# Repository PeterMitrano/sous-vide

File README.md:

# Sous-Vide

My first PCB design project.

### Final Results!

### Materials

see [sous-vide_bom.csv](./kicad_proj/sous-vide_bom_0.3.csv)

### Schematic

see [sous-vide.sch](./kicad_proj/sous-vide.sch)

### PCB

see [sous-vide.kicad_pcb](./kicad_proj/sous-vide.kicad_pcb)

Mains power is scary. I used this to calculate trace width/clearance: http://www.desmith.net/NMdS/Electronics/TraceWidth.html

### Revision Notes

 - Hole size of screw terminals are too small. Should be 1.8542mm
 - Screw terminals are a bad idea, use IEC connector
 - Higher power heater
 - Buzzer/Dinger!
 - One wire for thermistor/heater
 - Something to stir the water around
 - Label on V+ and V- on heater are backwards (J1)
 - Button footprint is wrong

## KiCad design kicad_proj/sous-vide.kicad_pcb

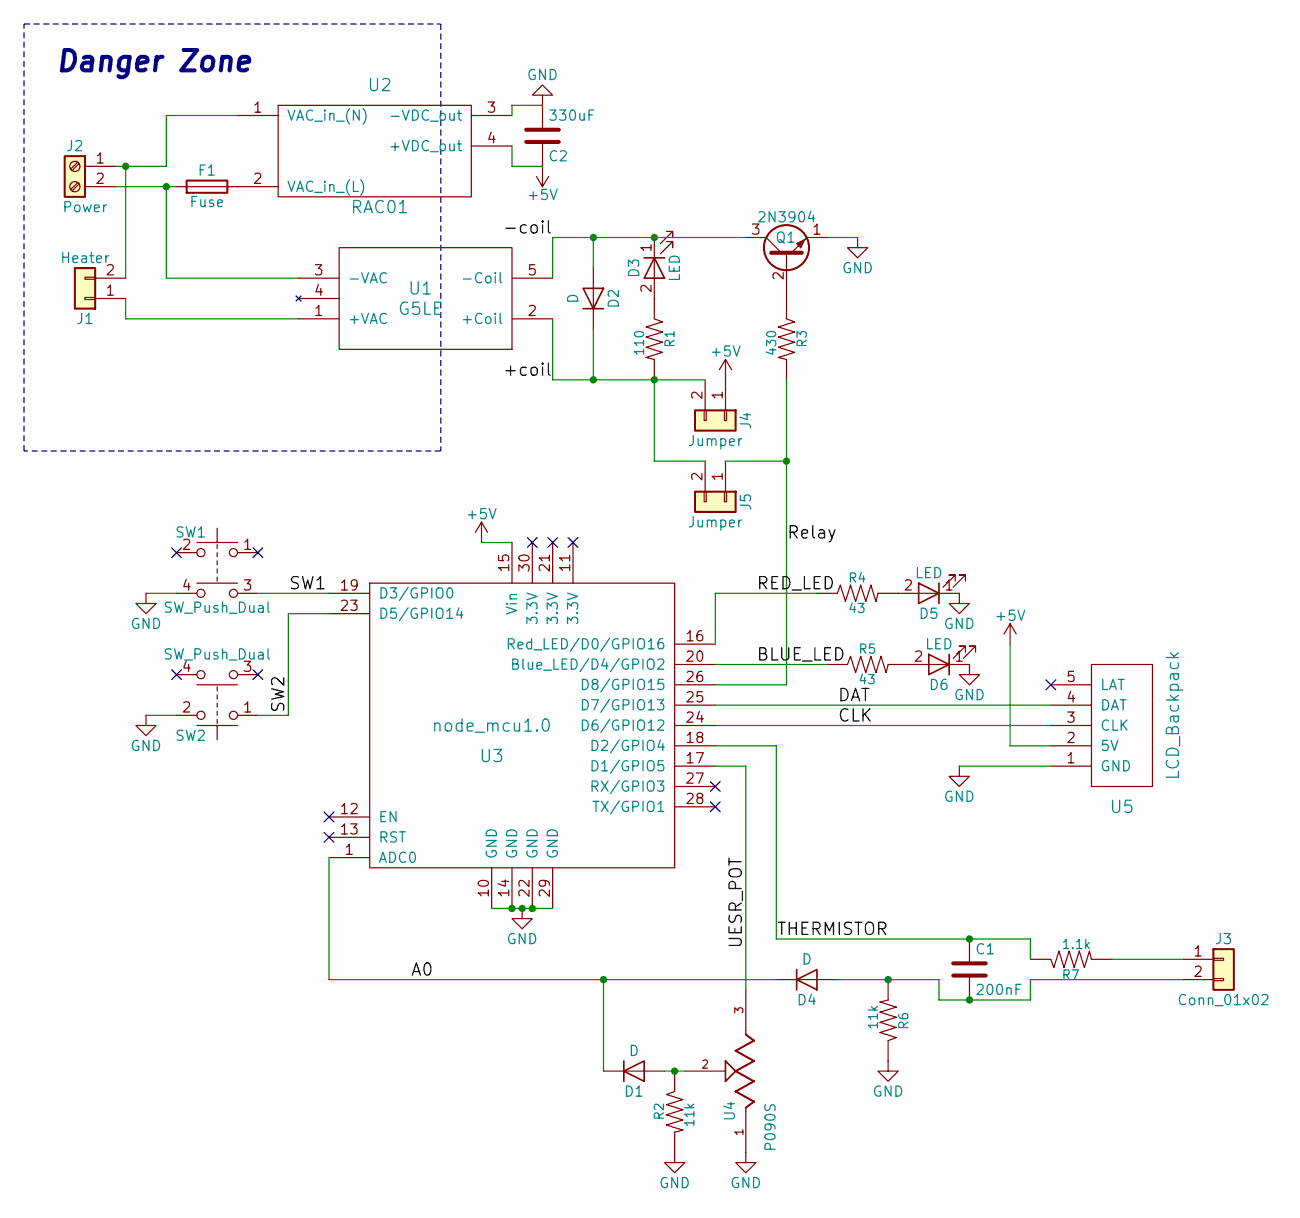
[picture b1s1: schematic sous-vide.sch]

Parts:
C1: 200nF; C_Disc_D4.3mm_W1.9mm_P5.00mm
C2: 330uF; CP_Radial_D8.0mm_P3.50mm
D1, D2, D4: D; D_DO-35_SOD27_P7.62mm_Horizontal; Part # 1N4148FS-ND
D3, D5, D6: LED; LED_D5.0mm; Part # 67-1105-ND
F1: Fuse; Fuse_Holder_65600001009
J1: Heater; NC6-P108-02
J2: Power; NC6-P108-02
J3: Conn_01x02; Pin_Header_Straight_1x02_Pitch2.54mm
J4, J5: Jumper; Pin_Header_Straight_1x02_Pitch2.54mm
Q1: 2N3904; TO-92_Molded_Narrow
R1: 110; R_Axial_DIN0207_L6.3mm_D2.5mm_P10.16mm_Horizontal
R2, R6: 11k; R_Axial_DIN0207_L6.3mm_D2.5mm_P10.16mm_Horizontal
R3: 430; R_Axial_DIN0207_L6.3mm_D2.5mm_P10.16mm_Horizontal
R4, R5: 43; R_Axial_DIN0207_L6.3mm_D2.5mm_P10.16mm_Horizontal
R7: 1.1k; R_Axial_DIN0207_L6.3mm_D2.5mm_P10.16mm_Horizontal
SW1, SW2: SW_Push_Dual; SW_TH_Tactile_Omron_B3F-10xx; Part # SW400-ND
U1: G5LE; Relay_SPDT_OMRON-G5LE-1
U2: RAC01; RAC01-05SC
U3: node_mcu1.0; NodeMCU_1_0
U4: P090S; P090S-THT_MNT
U5: LCD_Backpack; Pin_Header_Straight_1x05_Pitch2.54mm

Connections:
+5V: C2.1, J4.1, U2.4 (+VDC_out), U3.15 (Vin), U5.2 (5V)
/+coil: D2.1 (K), J4.2, J5.2, R1.2, U1.2 (+Coil)
/-coil: D2.2 (A), D3.1 (K), Q1.3 (C), U1.5 (-Coil)
/A0: D1.1 (K), D4.1 (K), U3.1 (ADC0)
/BLUE_LED: R5.1, U3.20 (Blue_LED/D4/GPIO2)
/CLK: U3.24 (D6/GPIO12), U5.3 (CLK)
/DAT: U3.25 (D7/GPIO13), U5.4 (DAT)
/RED_LED: R4.1, U3.16 (Red_LED/D0/GPIO16)
/Relay: J5.1, R3.2, U3.26 (D8/GPIO15)
/SW1: SW1.3, U3.19 (D3/GPIO0)
/SW2: SW2.1, U3.23 (D5/GPIO14)
/THERMISTOR: C1.1, R7.1, U3.18 (D2/GPIO4)
/UESR_POT: U3.17 (D1/GPIO5), U4.3 (CW)
GND: C2.2, D5.1 (K), D6.1 (K), Q1.1 (E), R2.2, R6.1, SW1.4, SW2.2, U2.3 (-VDC_out), U3.10 (GND), U3.14 (GND), U3.22 (GND), U3.29 (GND), U4.1 (CCW), U5.1 (GND)
unnamed: C1.2, D4.2 (A), J3.2, R6.2
unnamed: D1.2 (A), R2.1, U4.2 (S)
unnamed: D3.2 (A), R1.1
unnamed: D5.2 (A), R4.2
unnamed: D6.2 (A), R5.2
unnamed: F1.1, U2.2 (VAC_in_(L))
unnamed: F1.2, J2.2, U1.3 (-VAC)
unnamed: J1.1, U1.1 (+VAC)
unnamed: J1.2, J2.1, U2.1 (VAC_in_(N))
unnamed: J3.1, R7.2
unnamed: Q1.2 (B), R3.1

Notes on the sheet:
Danger Zone

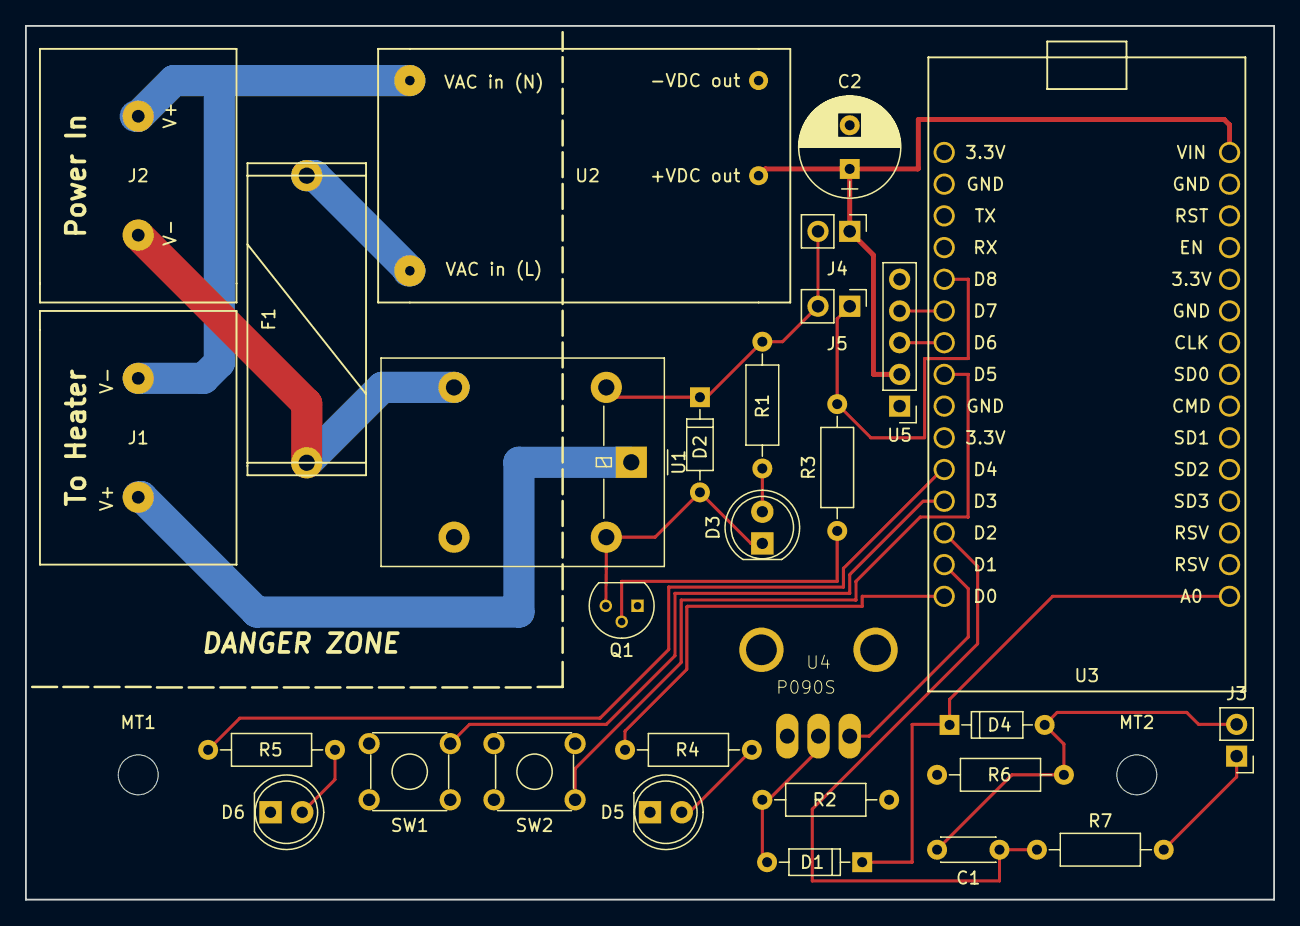
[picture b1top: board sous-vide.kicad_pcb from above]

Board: 2 copper layers, 100.0 x 70.0 mm, 31 parts (0 on the bottom side), 25 nets.

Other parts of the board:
MT1, MT2: MountingHole_3.2mm_M3

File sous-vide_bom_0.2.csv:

Component,Description,Part,References,Value,Footprint,Quantity Per PCB,Datasheet,Part #,Field8,Field4,Field7,Field6,Field5
1,Unpolarized capacitor,C,C1,C,C_Disc_D4.3mm_W1.9mm_P5.00mm,1,,,,,,,
2,Diode,D,D1 D2 D4,D,D_DO-35_SOD27_P7.62mm_Horizontal,3,https://www.fairchildsemi.com/datasheets/1N/1N914.pdf,1N4148FS-ND,,,,,
3,LED generic,LED,D3 D5 D6,LED,LED_D5.0mm,3,http://www.lumex.com/content/files/ProductAttachment/SSL-LX5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,67-1105-ND,,,,,
4,"Generic connector, single row, 01x02",Conn_01x02,J1,Conn_01x02,NC6-P108-02,1,,,,,,,
5,"Generic screw terminal, single row, 01x02",Screw_Terminal_01x02,J2,Conn_01x02,NC6-P108-02,1,,,,,,,
6,"Generic connector, single row, 01x02",Conn_01x02,J3,Conn_01x02,Pin_Header_Straight_1x02_Pitch2.54mm,1,,,,,,,
7,"40V Vce, 0.2A Ic, NPN, Small Signal Transistor, TO-92",2N3904,Q1,2N3904,TO-92_Molded_Narrow,1,https://www.fairchildsemi.com/datasheets/MM/MMBT3904.pdf,,,,,,
8,Generic Resistor Package,RESISTOR0402,R7,1.1k,R_Axial_DIN0207_L6.3mm_D2.5mm_P10.16mm_Horizontal,1,,,,,,,
9,Generic Resistor Package,RESISTOR0402,R1,110,R_Axial_DIN0207_L6.3mm_D2.5mm_P10.16mm_Horizontal,1,,,,,,,
10,Generic Resistor Package,RESISTOR0402,R2 R6,11k,R_Axial_DIN0207_L6.3mm_D2.5mm_P10.16mm_Horizontal,2,,,,,,,
11,Generic Resistor Package,RESISTOR0402,R4 R5,43,R_Axial_DIN0207_L6.3mm_D2.5mm_P10.16mm_Horizontal,2,,,,,,,
12,"Push button switch, generic, symbol, four pins",SW_Push_Dual,SW1 SW2,SW_Push_Dual,SW_TH_Tactile_Omron_B3F-10xx,2,http://omronfs.omron.com/en_US/ecb/products/pdf/en-b3f.pdf,SW400-ND,,,,,
13,,G5LE,U1,G5LE,Relay_SPDT_OMRON-G5LE-1,1,https://media.digikey.com/pdf/Data%20Sheets/Omron%20PDFs/G5L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,,,,,,
14,,LCD_Backpack,U5,LCD_Backpack,Pin_Header_Straight_1x05_Pitch2.54mm,1,,,,,,,
15,,P090S-04F20BR10K,U4,P090S,P090S-THT_MNT,1,P090S-04F20BR10K,,TT Electronics/BI,Good,None,0.40 USD,Res Conductive Plastic POT 10K Ohm 20% 0.03W 1(Elec)/1(Mech)Turn 6mm (11.4 X 12.65 X 23mm) Pin Bracket Mount/Through ...
16,,RAC01,U2,RAC01,RAC01-05SC,1,https://www.recom-power.com/pdf/Powerline-AC-DC/RAC01_02-SC.pdf,,,,,,
17,,node_mcu1.0,U3,node_mcu1.0,NodeMCU_1_0,1,,,,,,,





Component Groups:,17
Component Count:,24
Fitted Components:,24
Number of PCBs:,1
Total components:,24
Schematic Version:,0.2
Schematic Date:,2017-12-28
BoM Date:,Mon 01 Jan 2018 16:54:34 EST
Schematic Source:,/home/peter/Projects/sous-vide/sous-vide.sch
KiCad Version:,Eeschema 4.0.7-e2-6376~58~ubuntu16.04.1

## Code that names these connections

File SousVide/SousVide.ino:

#include <Wire.h>

const unsigned int RED_LED = D0;
const unsigned int BLUE_LED = D4;
const unsigned int SW1 = D3;
const unsigned int SW2 = D5;
const unsigned int RELAY = D8;
const unsigned int DAT = D7;
const unsigned int CLK = D6;
const unsigned int POT = D1;
const unsigned int THRM = D2;

unsigned long t = 0;
bool relay_state = false;

void setup() {
  pinMode(RED_LED, OUTPUT);
  pinMode(BLUE_LED, OUTPUT);
  pinMode(SW1, INPUT_PULLUP);
  pinMode(SW2, INPUT_PULLUP);
  pinMode(RELAY, OUTPUT);
  Wire.begin(DAT, CLK);
  pinMode(POT, OUTPUT);
  pinMode(THRM, OUTPUT);

  Serial.begin(9600);
  Serial.println("Setup.");

  t = millis();
}

void loop() {
  if (!digitalRead(SW1)) {
    digitalWrite(THRM, HIGH);
    digitalWrite(POT, LOW);
    digitalWrite(RED_LED, HIGH);
    unsigned int thm = analogRead(A0);
    Serial.print("sw1 ");
    Serial.print("thm: ");
    Serial.println(thm);

  }
  else {
    digitalWrite(RED_LED, LOW);
    digitalWrite(THRM, LOW);
    digitalWrite(POT, LOW);
  }

  if (!digitalRead(SW2)) {
    digitalWrite(THRM, LOW);
    digitalWrite(POT, HIGH);
    digitalWrite(BLUE_LED, HIGH);
    unsigned int pot = analogRead(A0);
    Serial.print("sw2 ");
    Serial.print("pot: ");
    Serial.println(pot);

  }
  else {
    digitalWrite(BLUE_LED, LOW);
    digitalWrite(THRM, LOW);
    digitalWrite(POT, LOW);
  }

  if (digitalRead(SW1) && digitalRead(SW2)) {
    Serial.print("no analog ");
    Serial.println(analogRead(A0));
  }

  Wire.beginTransmission(0x0);
  Wire.write(0xAA);
  Wire.endTransmission(true);

  unsigned long now = millis();
  if (now - t > 5000) {
    t = now;
    relay_state = !relay_state;
  }

  digitalWrite(RELAY, relay_state);

  delay(100);
}

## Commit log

2017-12-30 git init
    v0.1 done!
    haven't verified any of this works but the board is "done"
2017-12-30 added correct potentiometer footprint
2017-12-30 add freecad + step
2017-12-30 add new data sheet for LCD
2017-12-30 add the CAD
2017-12-30 started testing pins for GPIO
2017-12-31 redo entire schematic and layout
    now complete with danger zone!
2017-12-31 new PCB cad
2017-12-31 fix DRC issues
2017-12-31 0.1 -> 0.2
2017-12-31 update schematic pdf
2017-12-31 thermistor test code works
2017-12-31 fix resistor footprints
    - add dashed line
    - fix pot to use through hole mounting
    - checked everything for footprint errors
2017-12-31 new gerber
2017-12-31 add new datasheet
2017-12-31 add filter capacitor to thermistor
2017-12-31 tested analog-multiplexor circuit
    - it works!
2018-01-01 thermistor test "works"
    - if I understand correctly, R_Ref is calculated to be 1.1k
    - works for the one sample (Temp, ADC) I have
    - removed the 1k resistor on the relay circuit
2018-01-01 ready for Fab!
2018-01-02 V 0.3
    - added protection circuit and fuse
    - fixed LED indicator on relay circuit with Jeff's help
2018-01-02 fix power circuit
    - reroute
    - make board slightly bigger
2018-01-02 replot schematic
2018-01-02 breadboarded everything I could and tested
    - did not test I2C or Power Supply
    - relay state effects analog readings. bad!
2018-01-02 new schematic using NC7SB analog multiplexer
    - requires surface mount :(
    - re-annotated everything so routing will be very annoying
    Also, I was testing to see why/how relay load affected analog readings
    and I discovered a few odd things:
    - D4/GPIO2/Blue_LED does not light up. low voltage?
    - using a transistor on *just* the pot (instead of GPIO directly)
2018-01-04 Fix analog multiplex logic
    - tested with multimeter and oscilloscope and everything looks good
    - tested power supply, and it actually gives ~5.6 volts. This is fine
    fine for the MCU. Have to check if it's ok for the LCD
    - power supply powers the board successfully!
    - earlier issues were due to ground/power lines not connecting across
    the second half of the breadboard
2018-01-04 reverted to dio multiplexor because it works
    - measure 67mA on the coil, 5.31mA on the DIO
2018-01-04 regenerated and saved everything
    - no changes to pcb
    - generated gerber files, drill file, schematic and BOM
2018-01-04 added all pin labels to nodemcu footprint
    - add helpful labels on back
2018-01-04 rerouted wires so there are no breaks in the ground plane
2018-01-04 everything has been ordered!
2018-01-04 regenerated circuit board STEP
2018-01-04 remove STEP file cuz it's big
2018-01-04 added sous-vide via git(hub) LFS
2018-01-05 add wrl file
    - because solidworks is dying working on the step
2018-01-05 add wrl
2018-01-05 now trying STL
    solidworks still dying
2018-01-05 redid the case bottom
    - started work on case top but that might change so I'm not fussing
2018-01-05 moved arduino code
2018-01-05 remove old CAD formats
2018-01-05 project cleanup
    - untrack tmp kicad files
    - clone Wire library
2018-01-05 more project cleanup
    - no idea if I just broke the kicad project
2018-01-05 add proper IDEA project files
    - src: https://intellij-support.jetbrains.com/hc/en-us/articles/206544839-How-to-manage-projects-under-Version-Control-Systems
2018-01-08 trying to build with cmake
    - warning of an undefined symbol, haven't tested so idk if it works anyways
    - switching to platformio anyways probably
2018-01-08 moved to platformio + YCM
    - looks and builds great
2018-01-08 playing around with different code structures
    - event based?
    - state machine?
2018-01-08 going with simple state machine
2018-01-08 basic button debouncing/flow control works
2018-01-08 basic pot->time
2018-01-09 update to reflect final LED/pot positions
    - had to make the pot smaller because it conflicts with relay LED :(
2018-01-09 figured out how to use kicad stepup properly
    - demo for omron b3f_1000 button works perfectly!
    - just make/find STEP, load pcb footprint in freecad, align STEP with
    footprint, export WRL and STEP to the right folder (either in custom
    *.pretty library or in /usr/share/kicad/modules/packages3d/*.pretty
    library)
    - 3d preview in kicad will now work
2018-01-09 regenerated b3f for consistency and added relay g5le
2018-01-09 add screw terminals 3d
2018-01-09 apparently we also need the *1 files
2018-01-09 add RAC01 3d
2018-01-09 generated board to test progress
    - still missinged Diodes, LEDs, Resistors, Transistor
    - didn't do NodeMCU yet either
2018-01-09 regenerated whole board
    - everything in kicad viewer now shows up in freecad/step
    - still need to add STEP for NodeMCU and potentiometer
    - also may have lost my pot footprint among other things
2018-01-09 remove the libraries I deleted
    - schemtaics/footprints are cached thankfully
    - still step files for fuse, node mcu, pot
2018-01-09 add steps from tracepartsonline.net
    - removed unecessary renderings
2018-01-09 add nodemcu 3d
    - also add p090s step
2018-01-09 done added 3d models for v0.3
2018-01-09 all parts now in 3d step!
2018-01-09 imported new step cad into solidworks successfully
    - some small errors imported surface that I can easily fix
    - aslo added step for node mcu that I think is more accurate
2018-01-09 healed all bad surfaces
2018-01-09 reorganized cad files and deleted unecessary old files
2018-01-09 updated full case asm to use new board
    - looks amazing
    - still need to go back and fix node mcu model
2018-01-11 reorganize folders
2018-01-11 added code for PID and computing temperature
    - all untested still
2018-01-11 LCD works
    - need better string formatting capabilities
    - ranges of time/temp are good
2018-01-11 add i2c LCD backpack example
2018-01-11 add STLs and fix backpack model
    - backapck is now more accurate to physical object
2018-01-12 update parts for better tolerances
2018-01-23 fixed relay testing
    - runs at 50% duty cycle (1s period)
    - water heats up and nothing explodes
    - time/temp settings still need work
    - still no plans for thermistor yet
    - ned to reprint all the parts, consider laser cut top
2018-01-23 testing with the board
    - documenting the issues/bugs
2018-01-24 add 3d printable knob
2018-01-24 a bit of reorganizing and fluffing up
2018-01-25 redo CAD
    - ready for laser cutting top
    - reprint bottom
    - CNC mill the knob for extra fanciness
2018-01-25 clea lcd on state changes
    - rename blue to green to match real color
2018-01-25 better string formatting
2018-01-25 case bottom updates -> STL
2018-01-25 fix timing
    - add units to clarify
    - turns out code is slow and loop time is ~50ms
2018-01-25 fix time/temp formatting
    - increase min/max cooking duration
    - lcd.clear() does not work?
2018-01-26 added button holder
2018-01-29 recorded temperature data
2018-01-29 derived formula from data and put it in code
    - the physics based formula doesn't make any sense on my real data
2018-01-29 fix holes to power terminals
    - also make a few things thicker
2018-01-29 new button holder
2018-01-29 updated button holder again
2018-01-30 updates to 3d models
    - wider 3d printed knob
    - more curves/thicker stuff in base
2018-01-30 add stl for case bottom v3
2018-02-04 everything actually works!
    - need to add a "preheating" state
2018-02-04 reworked event handling
    - less frequenty updates of LCD
    - fast loop rate for buttons/heater control
2018-02-04 turns out I got the thermistor circuit wrong
    so I updated the schematic even though I'm definitely not ordering a new board just for that.
2018-02-04 tweaked values
2018-02-04 small param tweaks
    - fix wrapping error
2018-02-10 First test went ok, eggs were too hard boiled
    - added integral resetting
2018-02-10 Add code to finish when time runs out
2018-02-10 fixed end condition
    TODO:
    - should include a "add more time" option?
    - INTERNET!!!!
2018-02-11 This shit actually works!
    - revert minimimu time change
2018-02-11 work on documentation
2018-02-11 smaller imgs
2018-02-13 Add preheating step
2018-02-20 implement web server for logging temperature!
2018-02-21 implement max deque size
2018-02-21 fix controller
2018-02-22 automatically start once at temp
2018-03-04 Only wait 10 seconds max wait for WiFi
2018-03-04 add selection of wifi from menu
    - remembers wifi on reboot
2018-03-04 fix lcd clear
2018-03-04 untested 'fixes' to mdns
    - remove hardcoded password
    - lower P gain a bit
2018-03-06 wait longer for wifi
2018-03-07 revert temp constants
    - checked against real digital thermometer and it was saying 150 when
    it was 165
